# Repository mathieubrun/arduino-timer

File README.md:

# arduino timer

WIP : Built the first version of the board. Some adjustment needed, see [Lessons learned](#Lessons-learned).

## Usage

TODO

## Schema

## Board

## Code features

TODO

### Lessons learned

- add markings on silkscreen with polarities when applicable
- check component orientation: rev3 of the board was born because the 7 segments were upside down
- check component sizes twice: I used the wrong capacitor footprint
- check that components on both sides of the board can fit: the 7 segments display feets were on top of pads of the resistors on the other side.
- check pin pitch twice: the power connector had 1mm pitch instead of 0.1".
- check side of enclosure before cutting, twice: of course I cut the wrong side...
- for components with wiring like the encoder, double check correct soldering
- [a buzzer may require a resistor](https://electronics.stackexchange.com/questions/6500/connecting-piezo-buzzer-with-bjt) !

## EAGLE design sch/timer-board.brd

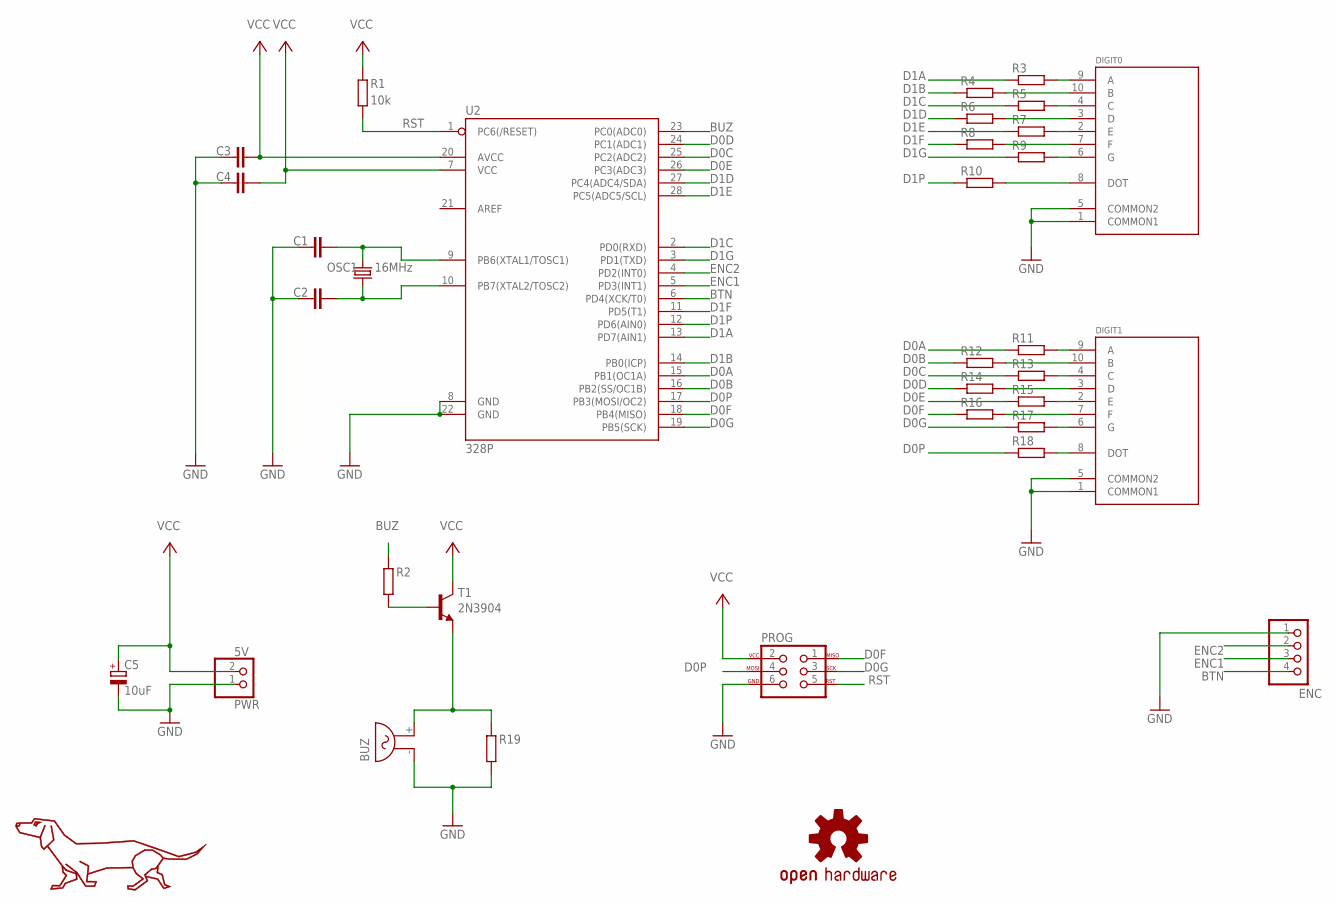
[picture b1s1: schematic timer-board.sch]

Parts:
BUZ: BUZZER
C1, C2: 22pF; C025-024X044
C3, C4: 0.1uF; C025-024X044
C5: 10uF; E2,5-6
DIGIT0, DIGIT1: 7_SEGMENT_DISPLAY; 7_SEGMENT_1.8_INCH
ENC: CONN_1X5; 1X04_LOCK_JST
LOGO1: OSHW-LOGOL; OSHW-LOGO-L
OSC1: 16MHz; HC49US
PROG: AVR_SPI_PROG_3X22X3_LOCK; 2X3_LOCK
PWR: 5V; 1X02_LOCK_JST
R1: 10k; 0207/10
R2, R3, R4, R5, R6, R7, R8, R9, R10, R11, R12, R13, R14, R15, R16, R17, R18, R19: R-EU_0207/10; 0207/10
T1: 2N3904; TO92
U2: 328P; DIP28
U$1: LOGO_DOG

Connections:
BTN: ENC.4, U2.6 (PD4(XCK/T0))
BUZ: R2.2, U2.23 (PC0(ADC0))
D0A: R11.1, U2.15 (PB1(OC1A))
D0B: R12.1, U2.16 (PB2(SS/OC1B))
D0C: R13.1, U2.25 (PC2(ADC2))
D0D: R14.1, U2.24 (PC1(ADC1))
D0E: R15.1, U2.26 (PC3(ADC3))
D0F: PROG.1, R16.1, U2.18 (PB4(MISO))
D0G: PROG.3, R17.1, U2.19 (PB5(SCK))
D0P: PROG.4, R18.1, U2.17 (PB3(MOSI/OC2))
D1A: R3.1, U2.13 (PD7(AIN1))
D1B: R4.1, U2.14 (PB0(ICP))
D1C: R5.1, U2.2 (PD0(RXD))
D1D: R6.1, U2.27 (PC4(ADC4/SDA))
D1E: R7.1, U2.28 (PC5(ADC5/SCL))
D1F: R8.1, U2.11 (PD5(T1))
D1G: R9.1, U2.3 (PD1(TXD))
D1P: R10.1, U2.12 (PD6(AIN0))
ENC1: ENC.3, U2.5 (PD3(INT1))
ENC2: ENC.2, U2.4 (PD2(INT0))
GND: BUZ.- (1), C1.1, C2.1, C3.2, C4.2, C5.-, DIGIT0.1 (COMMON1), DIGIT0.5 (COMMON2), DIGIT1.1 (COMMON1), DIGIT1.5 (COMMON2), ENC.1, PROG.6, PWR.1, R19.1, U2.8 (GND), U2.22 (GND)
unnamed: DIGIT0.9 (A), R3.2
unnamed: DIGIT0.10 (B), R4.2
unnamed: DIGIT0.4 (C), R5.2
unnamed: DIGIT0.3 (D), R6.2
unnamed: DIGIT0.2 (E), R7.2
unnamed: DIGIT0.7 (F), R8.2
unnamed: DIGIT0.6 (G), R9.2
unnamed: DIGIT0.8 (DOT), R10.2
unnamed: R2.1, T1.2 (B)
unnamed: DIGIT1.9 (A), R11.2
unnamed: DIGIT1.10 (B), R12.2
unnamed: DIGIT1.4 (C), R13.2
unnamed: DIGIT1.3 (D), R14.2
unnamed: DIGIT1.2 (E), R15.2
unnamed: DIGIT1.7 (F), R16.2
unnamed: DIGIT1.6 (G), R17.2
unnamed: DIGIT1.8 (DOT), R18.2
unnamed: BUZ.+ (2), R19.2, T1.3 (E)
RST: PROG.5, R1.1, U2.1 (PC6(/RESET))
VCC: C3.1, C4.1, C5.+, PROG.2, PWR.2, R1.2, T1.1 (C), U2.7 (VCC), U2.20 (AVCC)
XTAL1: C1.2, OSC1.2, U2.9 (PB6(XTAL1/TOSC1))
XTAL2: C2.2, OSC1.1, U2.10 (PB7(XTAL2/TOSC2))

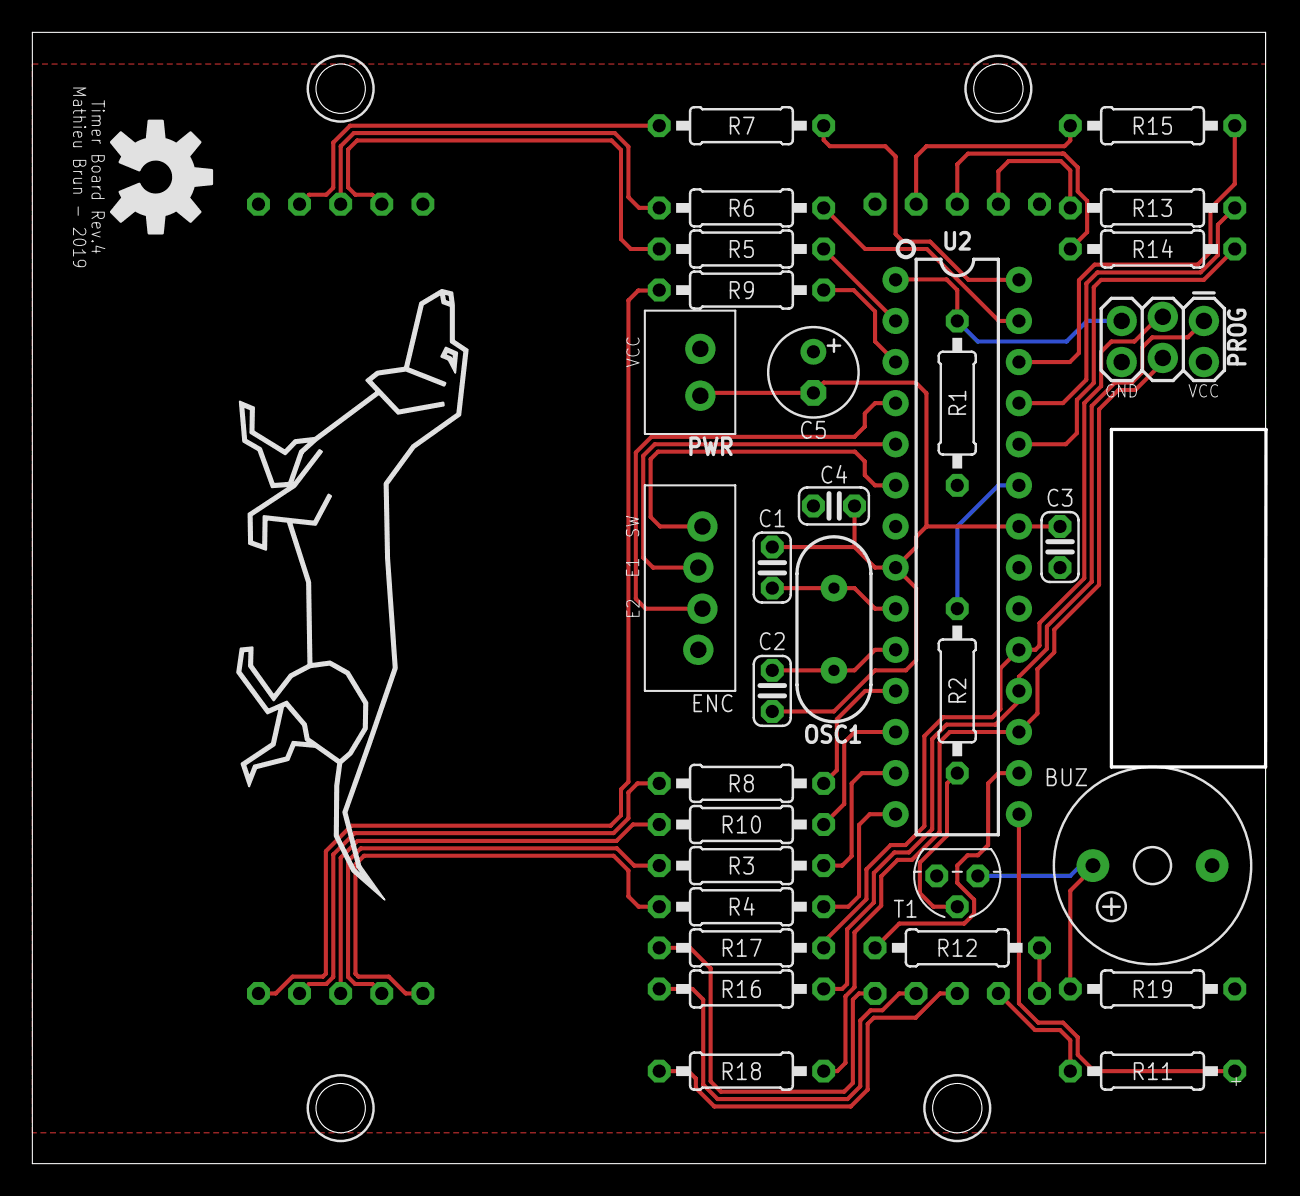
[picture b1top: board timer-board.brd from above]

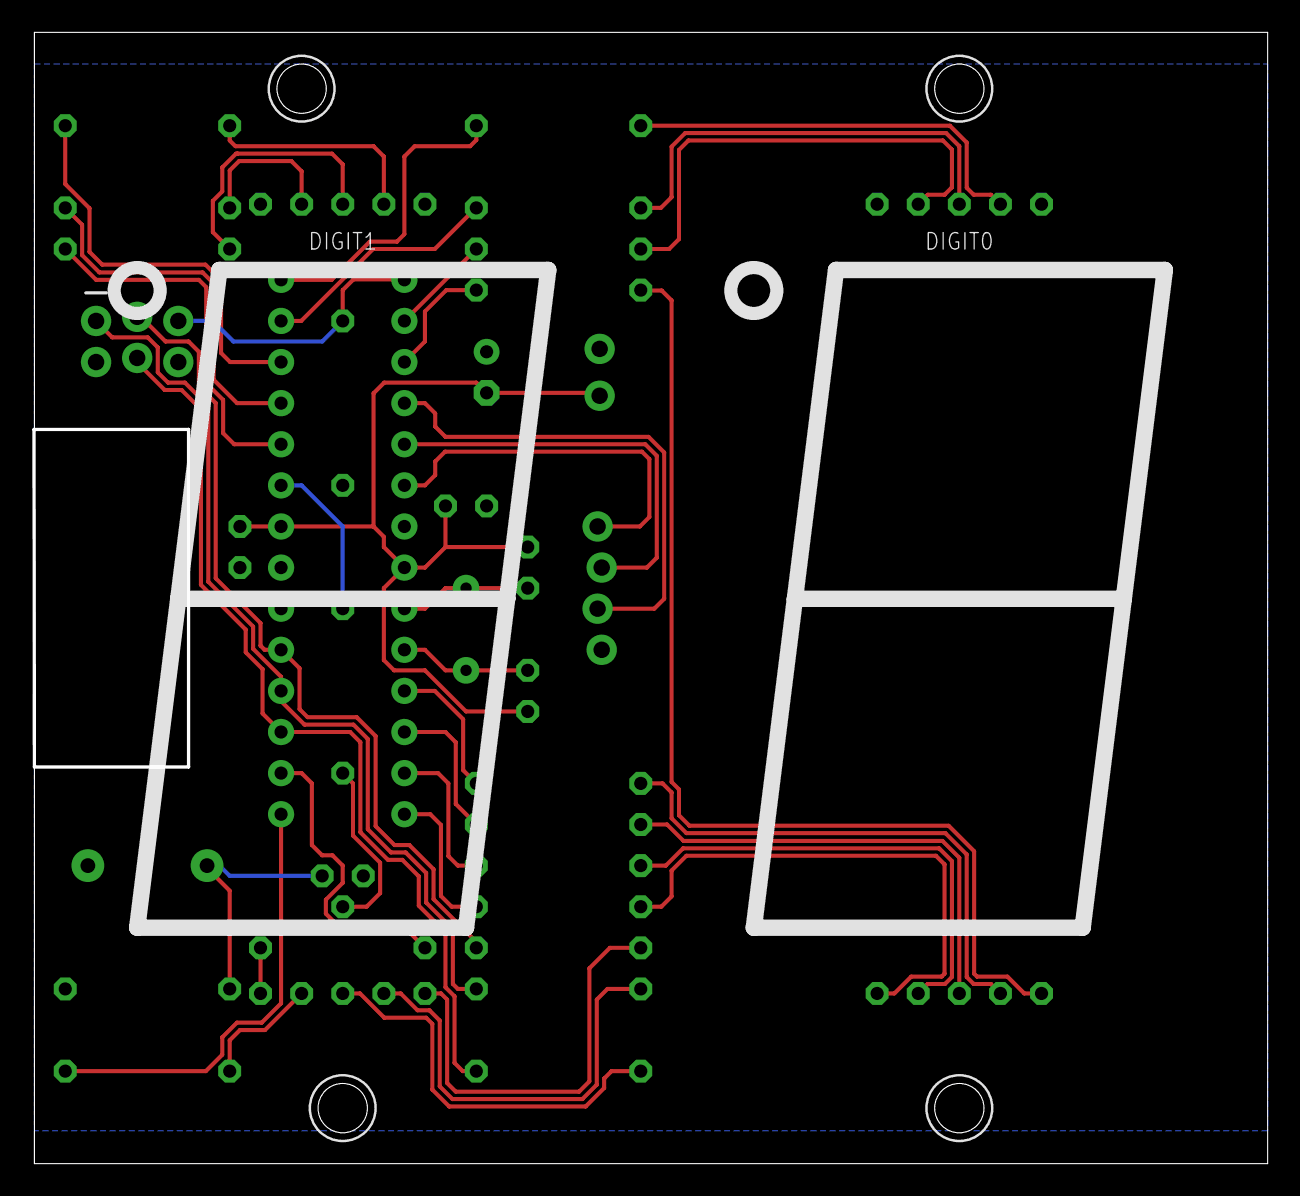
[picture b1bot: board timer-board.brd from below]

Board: 2 copper layers, 76.1 x 69.7 mm, 35 parts (2 on the bottom side), 43 nets.

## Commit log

2018-08-16 Repository init
2018-08-16 Added SCAD concept
2018-09-04 updated concept with new sizes
2018-09-04 added board schematic
2018-09-05 Cleaned up schematic
2018-09-11 Added licence file
2018-09-15 Added exported CAM files to gitignore
2018-09-15 Updated schematic to use new parts Added PCB first version
2018-09-16 PCB : better label positioning
2018-09-16 PCB : Added some logos
2018-09-16 PCB : Fixed resistor label
2018-09-17 PCB : Updated dog logo
2018-09-18 SCH : Added frame
2018-10-23 feat: updated board to smaller layout
2018-10-23 feat: reduced board edge clearance
2018-11-03 feat: pcb added holes
2019-06-24 Added readme and pretty pictures
2019-08-01 refactoring: reworked routing
2019-08-09 refactoring: finalized routing
2019-09-17 refactoring: added vcc pour, updated capacitors footprints fix: correct orientation of 7segment displays
2020-06-01 fix: clearance around milling, moved resistors, removed buzzer resistor

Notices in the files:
parts and their libraries:
SparkFun-Connectors: Licensing: Creative Commons ShareAlike 4.0 International - https://creativecommons.org/licenses/by-sa/4.0
